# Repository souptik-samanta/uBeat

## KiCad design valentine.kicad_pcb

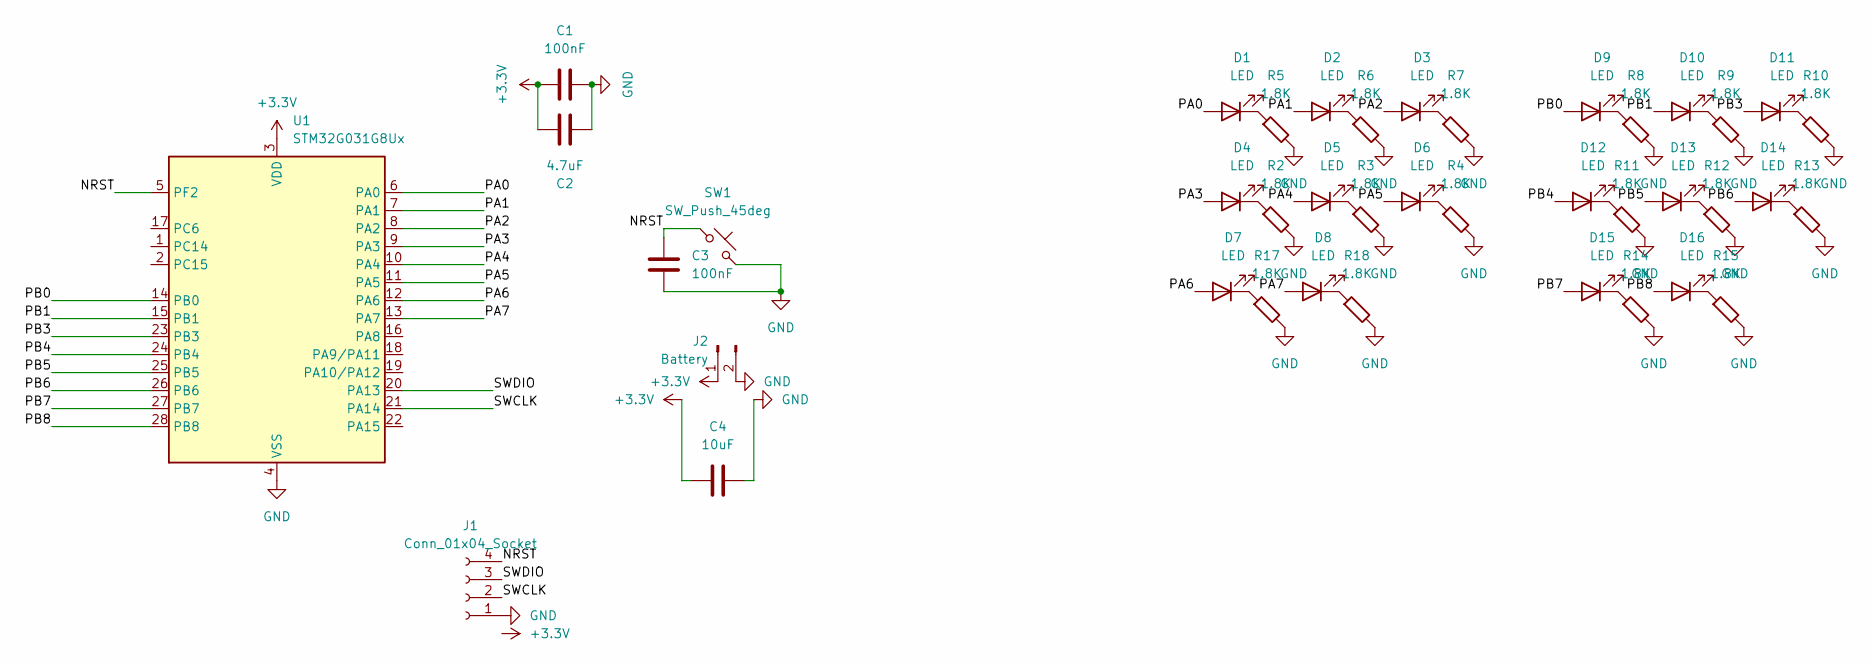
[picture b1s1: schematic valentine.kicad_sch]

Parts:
C1, C3: 100nF; C_0603_1608Metric
C2: 4.7uF; C_0805_2012Metric
C4: 10uF; C_0805_2012Metric
D1, D2, D3, D4, D5, D6, D7, D8, D9, D10, D11, D12, D13, D14, D15, D16: LED; LED_0603_1608Metric
J1: Conn_01x04_Socket; PinSocket_2x02_P1.27mm_Vertical_SMD
J2: Battery; PinHeader_1x02_P1.00mm_Vertical_SMD_Pin1Right
R2, R3, R4, R5, R6, R7, R8, R9, R10, R11, R12, R13, R14, R15, R17, R18: 1.8K; R_0402_1005Metric
SW1: SW_Push_45deg; SW_Push_SPST_NO_Alps_SKRK
U1: STM32G031G8Ux; QFN-28_4x4mm_P0.5mm

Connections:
+3.3V: C1.1, C2.1, C4.2, J2.1, U1.3 (VDD)
/NRST: C3.2, J1.4, SW1.1, U1.5 (PF2)
/PA0: D1.2 (A), U1.6 (PA0)
/PA1: D2.2 (A), U1.7 (PA1)
/PA2: D3.2 (A), U1.8 (PA2)
/PA3: D4.2 (A), U1.9 (PA3)
/PA4: D5.2 (A), U1.10 (PA4)
/PA5: D6.2 (A), U1.11 (PA5)
/PA6: D7.2 (A), U1.12 (PA6)
/PA7: D8.2 (A), U1.13 (PA7)
/PB0: D9.2 (A), U1.14 (PB0)
/PB1: D10.2 (A), U1.15 (PB1)
/PB3: D11.2 (A), U1.23 (PB3)
/PB4: D12.2 (A), U1.24 (PB4)
/PB5: D13.2 (A), U1.25 (PB5)
/PB6: D14.2 (A), U1.26 (PB6)
/PB7: D15.2 (A), U1.27 (PB7)
/PB8: D16.2 (A), U1.28 (PB8)
/SWCLK: J1.2, U1.21 (PA14)
/SWDIO: J1.3, U1.20 (PA13)
GND: C1.2, C2.2, C3.1, C4.1, J1.1, J2.2, R2.2, R3.2, R4.2, R5.2, R6.2, R7.2, R8.2, R9.2, R10.2, R11.2, R12.2, R13.2, R14.2, R15.2, R17.2, R18.2, SW1.2, U1.4 (VSS)
unnamed: D1.1 (K), R5.1
unnamed: D2.1 (K), R6.1
unnamed: D3.1 (K), R7.1
unnamed: D4.1 (K), R2.1
unnamed: D5.1 (K), R3.1
unnamed: D6.1 (K), R4.1
unnamed: D7.1 (K), R17.1
unnamed: D8.1 (K), R18.1
unnamed: D9.1 (K), R8.1
unnamed: D10.1 (K), R9.1
unnamed: D11.1 (K), R10.1
unnamed: D12.1 (K), R11.1
unnamed: D13.1 (K), R12.1
unnamed: D14.1 (K), R13.1
unnamed: D15.1 (K), R14.1
unnamed: D16.1 (K), R15.1

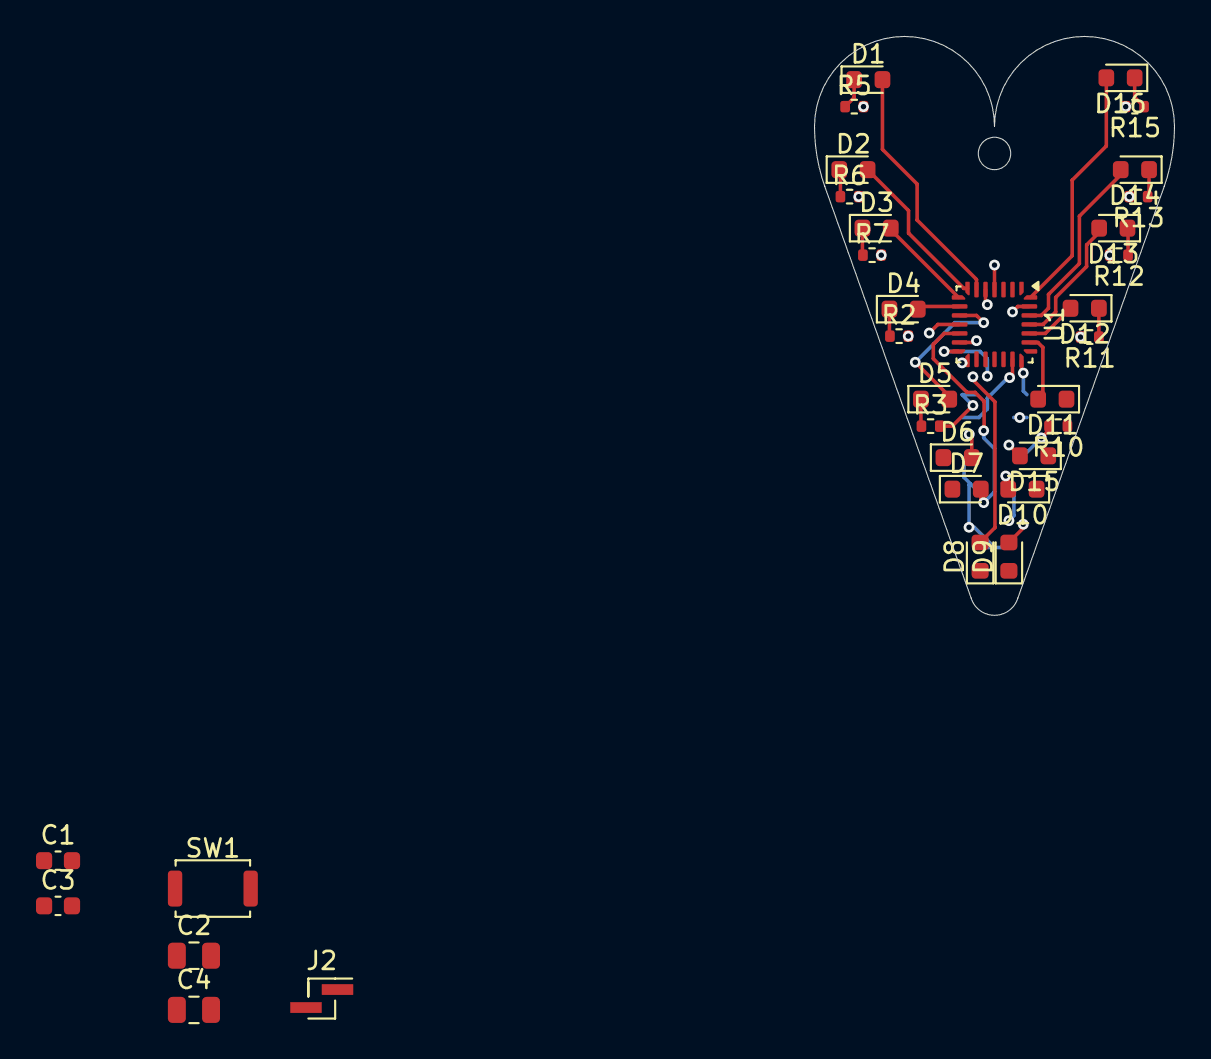
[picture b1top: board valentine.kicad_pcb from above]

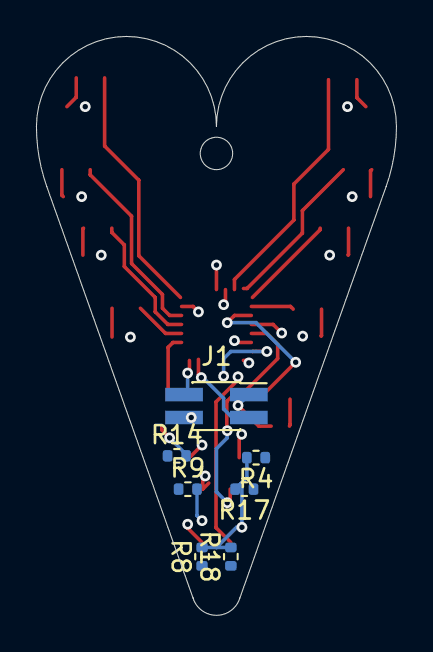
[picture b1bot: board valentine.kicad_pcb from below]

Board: 4 copper layers, 20.0 x 32.2 mm, 40 parts (7 on the bottom side), 37 nets.

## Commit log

2026-02-13 schmatic
2026-02-13 pcb design done ,,design as in where to put what i made a grid
2026-02-13 pcb routing
